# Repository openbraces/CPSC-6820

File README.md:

# CPSC-6820 Classwork

## Resources

- For composing LaTeX documents, VScode with [LaTeX Workshop](https://marketplace.visualstudio.com/items?itemName=James-Yu.latex-workshop) can be used. I personally have a full TeX Live distribution installed on my machine.

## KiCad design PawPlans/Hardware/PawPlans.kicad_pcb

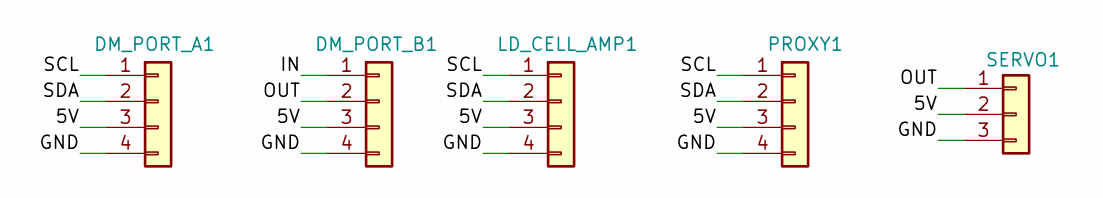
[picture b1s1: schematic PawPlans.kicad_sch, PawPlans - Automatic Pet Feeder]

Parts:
DM_PORT_A1: Conn_01x04; PinHeader_1x04_P2.54mm_Vertical
DM_PORT_B1: Conn_01x04; PinHeader_1x04_P2.54mm_Vertical
LD_CELL_AMP1: Conn_01x04; PinHeader_1x04_P2.54mm_Vertical
PROXY1: Conn_01x04; PinHeader_1x04_P2.54mm_Vertical
SERVO1: Conn_01x03; PinHeader_1x03_P2.54mm_Vertical

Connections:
/5V: DM_PORT_A1.3 (5V), DM_PORT_B1.3 (5V), LD_CELL_AMP1.3 (5V), PROXY1.3 (5V), SERVO1.2 (5V)
/GND: DM_PORT_A1.4 (GND), DM_PORT_B1.4 (GND), LD_CELL_AMP1.4 (GND), PROXY1.4 (GND), SERVO1.3 (GND)
/IN: DM_PORT_B1.1 (IN)
/OUT: DM_PORT_B1.2 (OUT), SERVO1.1 (SGN)
/SCL: DM_PORT_A1.1 (SCL), LD_CELL_AMP1.1 (SCL), PROXY1.1 (SDA)
/SDA: DM_PORT_A1.2 (SDA), LD_CELL_AMP1.2 (SDA), PROXY1.2 (SDA)

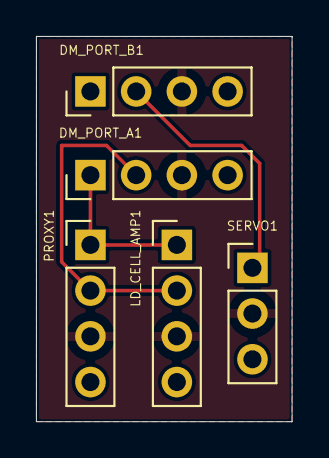
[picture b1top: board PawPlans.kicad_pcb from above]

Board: 2 copper layers, 14.2 x 21.4 mm, 5 parts (0 on the bottom side), 5 nets.

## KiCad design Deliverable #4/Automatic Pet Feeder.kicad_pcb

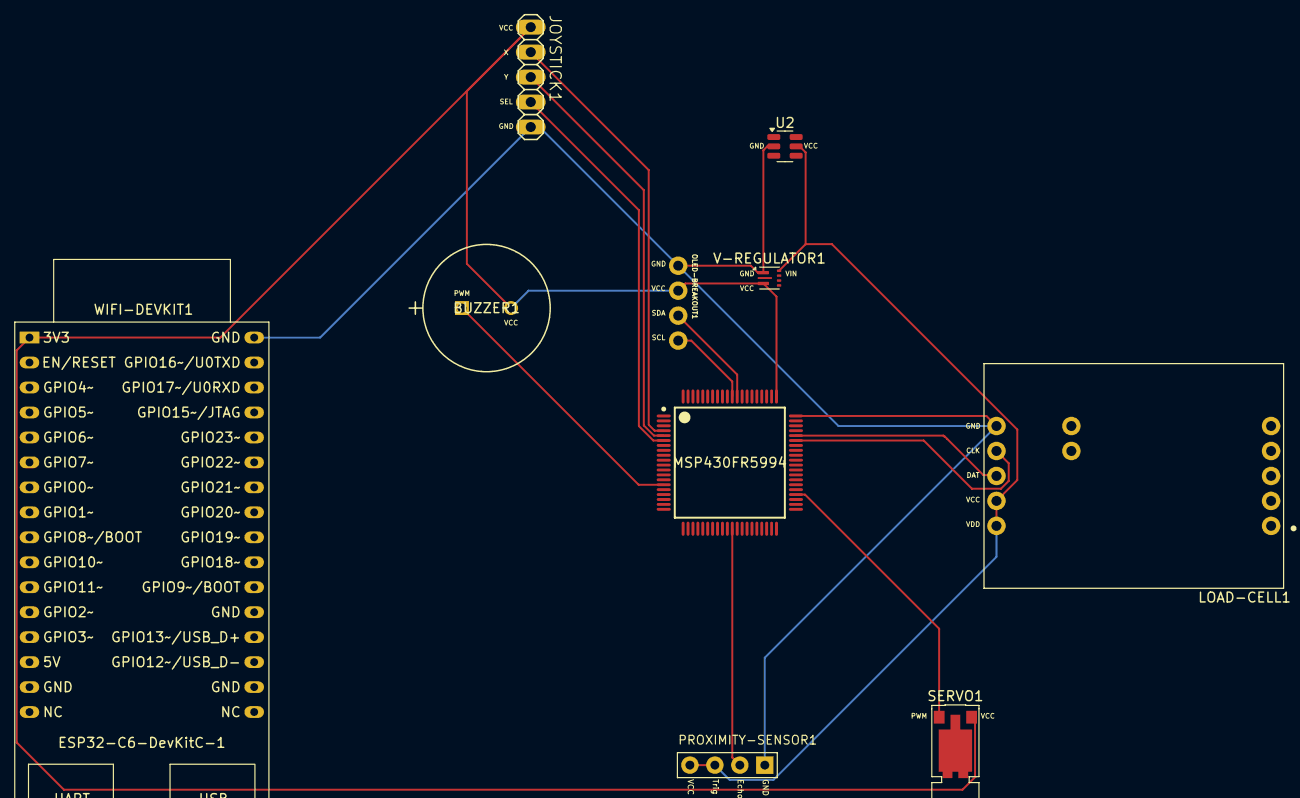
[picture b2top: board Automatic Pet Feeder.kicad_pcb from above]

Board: 2 copper layers, 10 parts (0 on the bottom side), 13 nets.

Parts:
BUZZER1: PS1240P02BT; XTAL_PS1240P02BT_TDK
JOYSTICK1: 1X05
LOAD-CELL1: SEN-13879; SPARKFUN_SEN-13879
MSP430FR5994: MSP430FR5994IPN; PN0080A_N
OLED-BREAKOUT1: SPARKX_1X04_NO_SILK
PROXIMITY-SENSOR1: HC-SR04_FOOTPRINT
SERVO1: Motor_Servo; Vybronics_VZ30C1T8219732L
U2: TPS2513; SOT-23-6
V-REGULATOR1: TPS61022; Texas_RWU0007A_VQFN-7_2x2mm_P0.5mm
WIFI-DEVKIT1: ESP32-C6-DevKitC-1

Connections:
/GND: JOYSTICK1.5, LOAD-CELL1.6 (GND), MSP430FR5994.60 (DVSS1), OLED-BREAKOUT1.1 (GND), PROXIMITY-SENSOR1.GND, U2.2 (GND), V-REGULATOR1.1 (GND), WIFI-DEVKIT1.32 (GND)
/SEL: JOYSTICK1.4, MSP430FR5994.6 (P3.2_A14_C14)
/VCC: BUZZER1.2, JOYSTICK1.1, MSP430FR5994.61 (DVCC1), OLED-BREAKOUT1.2 (VCC), SERVO1.2 (+), V-REGULATOR1.3 (VOUT), WIFI-DEVKIT1.1 (3V3)
/X: JOYSTICK1.2, MSP430FR5994.4 (P3.0_A12_C12)
/Y: JOYSTICK1.3, MSP430FR5994.5 (P3.1_A13_C13)
unnamed: LOAD-CELL1.7 (CLK), MSP430FR5994.55 (P5.2_UCB1CLK_TA4CLK)
unnamed: LOAD-CELL1.8 (DAT), MSP430FR5994.56 (P5.3_UCB1STE)
unnamed: LOAD-CELL1.9 (VCC), LOAD-CELL1.10 (VDD), PROXIMITY-SENSOR1.TRIG, PROXIMITY-SENSOR1.VCC (5V), U2.5 (IN), V-REGULATOR1.7 (VIN)
unnamed: MSP430FR5994.70 (P6.5_UCB3SOMI_UCB3SCL), OLED-BREAKOUT1.4 (SCL)
unnamed: MSP430FR5994.69 (P6.4_UCB3SIMO_UCB3SDA), OLED-BREAKOUT1.3 (SDA)
unnamed: MSP430FR5994.44 (P8.1), SERVO1.1 (PWM)
unnamed: MSP430FR5994.31 (P4.0_A8), PROXIMITY-SENSOR1.ECHO
unnamed: BUZZER1.1, MSP430FR5994.15 (P8.0)

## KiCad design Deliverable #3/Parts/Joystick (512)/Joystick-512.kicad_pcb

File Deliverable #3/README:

CPSC-6820 Deliverable #3
Team: Happy Pets
Teammates: Sriram Vishnubhotla, Logan Swoyer
Project: Automatic Pet Feeder
Project Repository: https://github.com/hexlambda/CPSC-6820/
Project Overview: A pet feeding device with fine-grained scheduling settings and mobile connectivity.
Parts:
Piezoelectric Buzzer (PS1240P02BT)
Joystick (512)
Load Cell Amplifier (SEN-13879)
Microcontroller (MSP430FR5994)
OLED Display + Breakout board (SSD1306)
Proximity Sensor (VL6180V1NR)
WiFi Module + Breakout board (WINC1500)

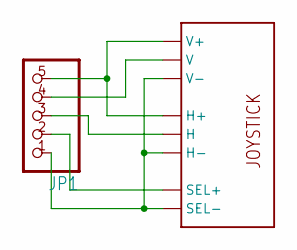
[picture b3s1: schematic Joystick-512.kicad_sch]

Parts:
JP1: PINHD-1X5; 1X05
U1: JOYSTICKPTH; JOYSTICK

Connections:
unnamed: JP1.5, U1.H1 (H+), U1.V1 (V+)
unnamed: JP1.1, U1.B2A (SEL-), U1.H3 (H-), U1.V3 (V-)
unnamed: JP1.4, U1.V2 (V)
unnamed: JP1.3, U1.H2 (H)
unnamed: JP1.2, U1.B1A (SEL+)

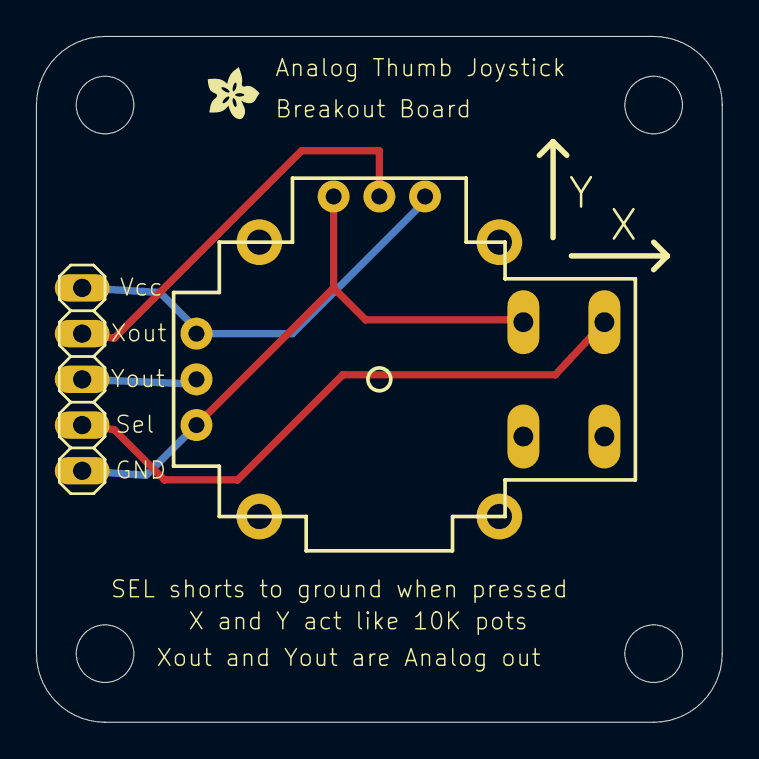
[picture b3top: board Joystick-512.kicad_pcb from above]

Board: 16 copper layers, 38.1 x 38.1 mm, 7 parts (0 on the bottom side), 5 nets.

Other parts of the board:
@HOLE0, @HOLE1, @HOLE2, @HOLE3: (no value)
U$1: ADAFRUIT200MIL

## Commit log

2025-02-02 Added deliverable #2 base files
2025-02-02 Added parts table
2025-02-03 Added state machine
2025-02-03 Added system description
2025-02-03 Added links to parts table
2025-02-03 added hardware section
2025-02-03 Adjusted directory structure and added UI figure
2025-02-03 Minor rewording and adjustments
2025-02-03 Added README and demo section, squashed commits to clean up
2025-02-04 Resources and minor adjustments
2025-02-04 Added content to presentation
2025-02-04 added wifi data sheet to document
2025-02-18 Added parts
2025-02-20 Added MCU to parts
2025-02-20 added library of parts for eaglecad
2025-02-20 added brd and schematic file
2025-02-20 Adjusted confusing file names, added EAGLE-compatible libs
2025-02-20 added servo to schematic
2025-02-20 Added deliverable #0 files
2025-02-20 Added missing EAGLE files, renamed files
2025-02-20 Reworked schematic
2025-02-20 Added deliverable #3 README
2025-02-27 Implement board
2025-02-27 added testing plan tex and pdf
2025-02-27 Added testing plan, tidied up deliverable #4 files
2025-03-13 Added PawPlans files, reworked board and schematic
2025-03-14 Completely revamped the schematic and PCB, cleaned up project files
2025-03-14 Added board title and credits to silkscreen
2025-03-14 Removed SparkFun OLED submodule from Deliverable #4
2025-03-14 Removed MSP430 footprints
2025-03-14 Adjusted the board, switched TDK piezo buzzer for a Murata
2025-03-23 added the platformIO project
2025-03-23 Reworked hardware (centered around M5Stack's DinMeter, ESP32), adjusted board and schematic
2025-03-23 Changed platform to ESP32-S3
2025-03-23 Adjusted dir structure
2025-03-23 Add M5DinMeter lib as dep, add barebones files
2025-03-23 Added header string formatting
2025-03-23 added the main menu
2025-03-24 Added clock menu string
2025-03-24 Added schedule menu string
2025-03-24 Added update_output_string to update
2025-03-24 Added scheduling logic
2025-03-24 Added .clang-format
2025-03-24 Reworked UI and scheduling code
2025-03-24 Fixed increment and decrement logic to use mod instead of min/max
2025-03-24 Added select switch statement for root
2025-03-25 Split source files, glued logic together
2025-03-25 More fixes, overall clean up
2025-03-25 Started test
2025-03-25 added more tests
2025-03-25 Added sensing code
2025-03-25 Reverted menu.cpp's accidental reversal
2025-03-25 Added testing.txt
2025-03-25 fixed testing.txt
2025-04-15 added stl file
2025-04-25 Deliverable #6a
2025-04-25 Switched to using ESP-IDF, implemented core logic
2025-04-30 Adjusted resting and dispense angles
